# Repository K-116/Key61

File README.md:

# Key61
A 60% keyboard that I can use for gaming, music and homework. The software i used was Kicad, Tinkercad (I swear ill learn fusion 360 at some point) and I used FREEcad to put it all together. Ive been wanting to make a keyboard for myself for a while now and I'm glad I could finally make one!

<h2>CAD</h2>

<H2>PCB</H2>

<H2>FULL MODEL</H2>

<H2>COMPLETED FULL PROJECT</H2>
ADD THIS WHEN COMPLETE.

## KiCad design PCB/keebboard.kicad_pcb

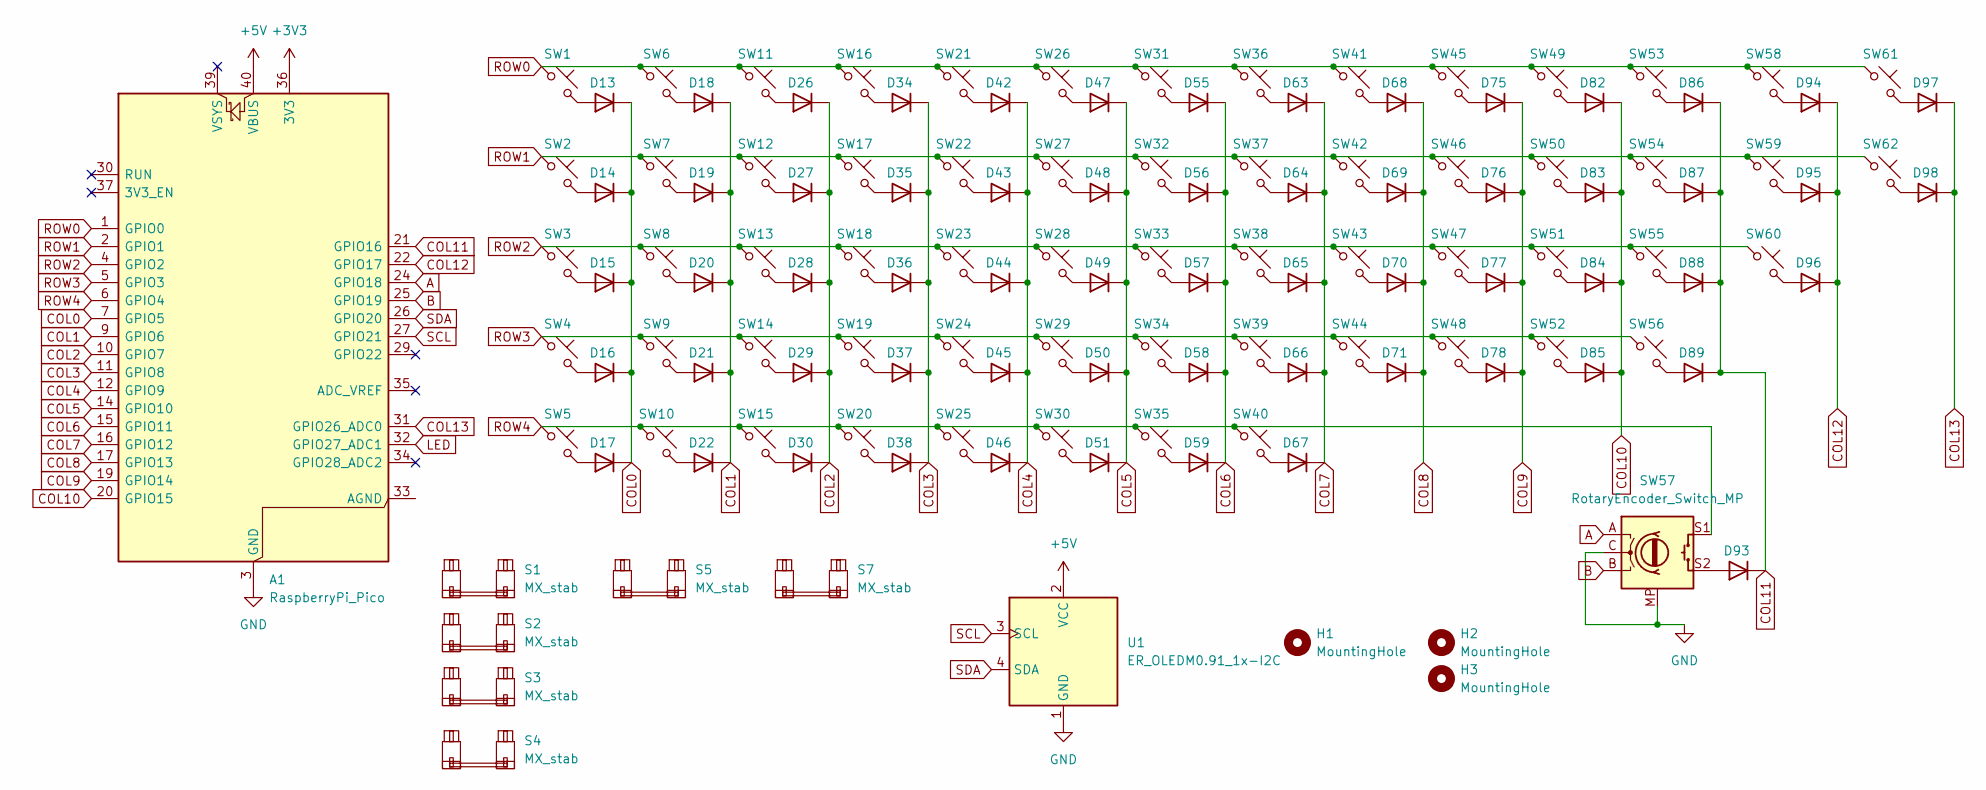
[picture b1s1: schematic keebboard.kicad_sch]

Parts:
A1: RaspberryPi_Pico; RaspberryPi_Pico_Common_Unspecified
D13, D14, D15, D16, D17, D18, D19, D20, D21, D22, D26, D27, D28, D29, D30, D34, D35, D36, D37, D38, D42, D43, D44, D45, D46, D47, D48, D49, D50, D51, D55, D56, D57, D58, D59, D63, D64, D65, D66, D67, D68, D69, D70, D71, D75, D76, D77, D78, D82, D83, D84, D85, D86, D87, D88, D89, D93, D94, D95, D96, D97, D98: 1N4148; D_DO-35_SOD27_P7.62mm_Horizontal
H1, H2, H3: MountingHole; MountingHole_2.1mm
S1, S3: MX_stab; STAB_MX_P_2.25u
S2: MX_stab; STAB_MX_P_6.25u
S4, S7: MX_stab; STAB_MX_2u
S5: MX_stab; STAB_MX_P_2.75u
SW1, SW2, SW3, SW4, SW5, SW6, SW7, SW8, SW9, SW10, SW11, SW12, SW13, SW14, SW15, SW16, SW17, SW18, SW19, SW20, SW21, SW22, SW23, SW24, SW25, SW26, SW27, SW28, SW29, SW30, SW31, SW32, SW33, SW34, SW35, SW36, SW37, SW38, SW39, SW40, SW41, SW42, SW43, SW44, SW45, SW46, SW47, SW48, SW49, SW50, SW51, SW52, SW53, SW54, SW55, SW56, SW58, SW59, SW61, SW62: SW_Push_45deg; SW_Cherry_MX_1.00u_PCB
SW57: RotaryEncoder_Switch_MP; RotaryEncoder_Alps_EC12E-Switch_Vertical_H20mm
SW60: SW_Push_45deg; SW_Cherry_MX_1.75u_PCB
U1: ER_OLEDM0.91_1x-I2C

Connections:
+3V3: A1.36 (3V3)
+5V: A1.40 (VBUS), U1.2 (VCC)
A: A1.24 (GPIO18), SW57.A
B: A1.25 (GPIO19), SW57.B
COL0: A1.7 (GPIO5), D13.1 (K), D14.1 (K), D15.1 (K), D16.1 (K), D17.1 (K)
COL1: A1.9 (GPIO6), D18.1 (K), D19.1 (K), D20.1 (K), D21.1 (K), D22.1 (K)
COL2: A1.10 (GPIO7), D26.1 (K), D27.1 (K), D28.1 (K), D29.1 (K), D30.1 (K)
COL3: A1.11 (GPIO8), D34.1 (K), D35.1 (K), D36.1 (K), D37.1 (K), D38.1 (K)
COL4: A1.12 (GPIO9), D42.1 (K), D43.1 (K), D44.1 (K), D45.1 (K), D46.1 (K)
COL5: A1.14 (GPIO10), D47.1 (K), D48.1 (K), D49.1 (K), D50.1 (K), D51.1 (K)
COL6: A1.15 (GPIO11), D55.1 (K), D56.1 (K), D57.1 (K), D58.1 (K), D59.1 (K)
COL7: A1.16 (GPIO12), D63.1 (K), D64.1 (K), D65.1 (K), D66.1 (K), D67.1 (K)
COL8: A1.17 (GPIO13), D68.1 (K), D69.1 (K), D70.1 (K), D71.1 (K)
COL9: A1.19 (GPIO14), D75.1 (K), D76.1 (K), D77.1 (K), D78.1 (K)
COL10: A1.20 (GPIO15), D82.1 (K), D83.1 (K), D84.1 (K), D85.1 (K)
COL11: A1.21 (GPIO16), D86.1 (K), D87.1 (K), D88.1 (K), D89.1 (K), D93.1 (K)
COL12: A1.22 (GPIO17), D94.1 (K), D95.1 (K), D96.1 (K)
COL13: A1.31 (GPIO26_ADC0), D97.1 (K), D98.1 (K)
GND: A1.3 (GND), A1.8 (GND), A1.13 (GND), A1.18 (GND), A1.23 (GND), A1.28 (GND), A1.38 (GND), SW57.C, SW57.MP, U1.1 (GND)
LED: A1.32 (GPIO27_ADC1)
unnamed: D13.2 (A), SW1.2
unnamed: D14.2 (A), SW2.2
unnamed: D15.2 (A), SW3.2
unnamed: D16.2 (A), SW4.2
unnamed: D17.2 (A), SW5.2
unnamed: D18.2 (A), SW6.2
unnamed: D19.2 (A), SW7.2
unnamed: D20.2 (A), SW8.2
unnamed: D21.2 (A), SW9.2
unnamed: D22.2 (A), SW10.2
unnamed: D26.2 (A), SW11.2
unnamed: D27.2 (A), SW12.2
unnamed: D28.2 (A), SW13.2
unnamed: D29.2 (A), SW14.2
unnamed: D30.2 (A), SW15.2
unnamed: D34.2 (A), SW16.2
unnamed: D35.2 (A), SW17.2
unnamed: D36.2 (A), SW18.2
unnamed: D37.2 (A), SW19.2
unnamed: D38.2 (A), SW20.2
unnamed: D42.2 (A), SW21.2
unnamed: D43.2 (A), SW22.2
unnamed: D44.2 (A), SW23.2
unnamed: D45.2 (A), SW24.2
unnamed: D46.2 (A), SW25.2
unnamed: D47.2 (A), SW26.2
unnamed: D48.2 (A), SW27.2
unnamed: D49.2 (A), SW28.2
unnamed: D50.2 (A), SW29.2
unnamed: D51.2 (A), SW30.2
unnamed: D55.2 (A), SW31.2
unnamed: D56.2 (A), SW32.2
unnamed: D57.2 (A), SW33.2
unnamed: D58.2 (A), SW34.2
unnamed: D59.2 (A), SW35.2
unnamed: D63.2 (A), SW36.2
unnamed: D64.2 (A), SW37.2
unnamed: D65.2 (A), SW38.2
unnamed: D66.2 (A), SW39.2
unnamed: D67.2 (A), SW40.2
unnamed: D68.2 (A), SW41.2
unnamed: D69.2 (A), SW42.2
unnamed: D70.2 (A), SW43.2
unnamed: D71.2 (A), SW44.2
unnamed: D75.2 (A), SW45.2
unnamed: D76.2 (A), SW46.2
unnamed: D77.2 (A), SW47.2
unnamed: D78.2 (A), SW48.2
unnamed: D82.2 (A), SW49.2
unnamed: D83.2 (A), SW50.2
unnamed: D84.2 (A), SW51.2
unnamed: D85.2 (A), SW52.2
unnamed: D86.2 (A), SW53.2
unnamed: D87.2 (A), SW54.2
unnamed: D88.2 (A), SW55.2
unnamed: D89.2 (A), SW56.2
unnamed: D93.2 (A), SW57.S2
unnamed: D94.2 (A), SW58.2
unnamed: D95.2 (A), SW59.2
unnamed: D96.2 (A), SW60.2
unnamed: D97.2 (A), SW61.2
unnamed: D98.2 (A), SW62.2
ROW0: A1.1 (GPIO0), SW1.1, SW6.1, SW11.1, SW16.1, SW21.1, SW26.1, SW31.1, SW36.1, SW41.1, SW45.1, SW49.1, SW53.1, SW58.1, SW61.1
ROW1: A1.2 (GPIO1), SW2.1, SW7.1, SW12.1, SW17.1, SW22.1, SW27.1, SW32.1, SW37.1, SW42.1, SW46.1, SW50.1, SW54.1, SW59.1, SW62.1
ROW2: A1.4 (GPIO2), SW3.1, SW8.1, SW13.1, SW18.1, SW23.1, SW28.1, SW33.1, SW38.1, SW43.1, SW47.1, SW51.1, SW55.1, SW60.1
ROW3: A1.5 (GPIO3), SW4.1, SW9.1, SW14.1, SW19.1, SW24.1, SW29.1, SW34.1, SW39.1, SW44.1, SW48.1, SW52.1, SW56.1
ROW4: A1.6 (GPIO4), SW5.1, SW10.1, SW15.1, SW20.1, SW25.1, SW30.1, SW35.1, SW40.1, SW57.S1
SCL: A1.27 (GPIO21), U1.3 (SCL)
SDA: A1.26 (GPIO20), U1.4 (SDA)

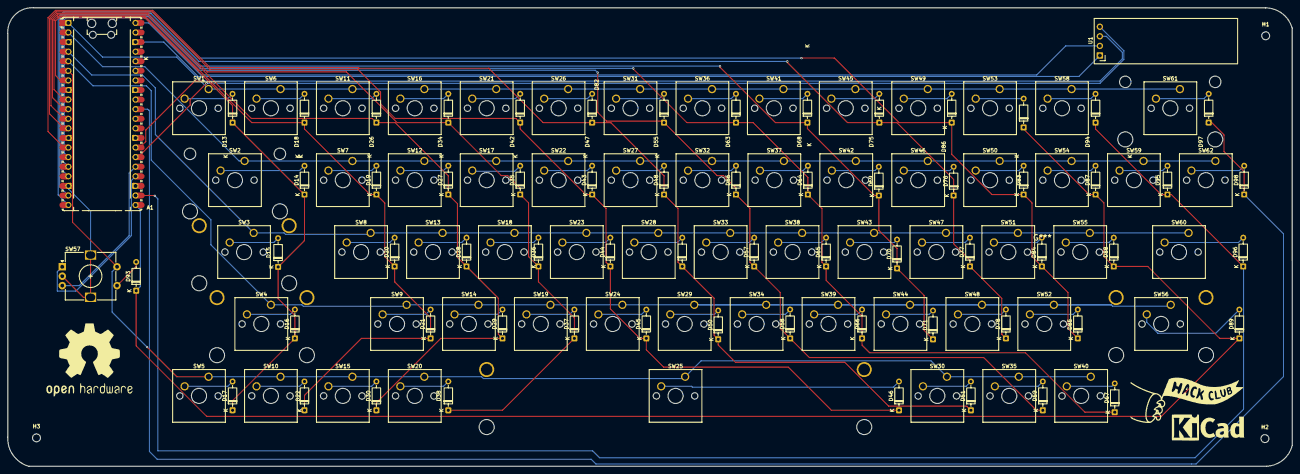
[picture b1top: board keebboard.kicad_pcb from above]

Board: 2 copper layers, 340.3 x 121.5 mm, 135 parts (0 on the bottom side), 87 nets.
